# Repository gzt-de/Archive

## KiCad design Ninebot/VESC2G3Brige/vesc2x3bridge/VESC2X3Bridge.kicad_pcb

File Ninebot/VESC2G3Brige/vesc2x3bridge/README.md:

# VESC2X3Bridge

This repository provides the PCB files for the VESC2X3Bridge board. It allows an almost plug-and-play installation, with minimal configuration required on both the VESC and Bridge sides.

Community Telegram channel [Ninebot Bridges](https://t.me/NinebotBridges)

[Demo Video with my Firmware](https://youtu.be/Sf85hNRvy-E)

Also check out this repository which is used to drive the lights on your X3 Series Scooter [LightBoard](https://gitea.overkill.cc/morss12/LightBoard.git)

# Features & Abilities

A simple overview of everything the VESC2G3Bridge can do.

## What Is It?

The VESC2X3Bridge is a project I started at the end of 2025. It aims to integrate the X3 Scooter Series from Ninebot into the world of VESC, an open-source project by Benjamin Vedder.
The VESC2G3Bridge is a small computer that sits between your scooter's motor controller (VESC) and its dashboard (G3). Without it, the dashboard and the motor controller don't understand each other — the bridge acts like a translator so they can work together.

## What It Does

### Shows Your Speed
The device reads how fast the motor is spinning and works out your actual riding speed. It then sends that number to the dashboard so you can see it while you ride.

### Shows Battery Level
It checks how much battery you have left and tells the dashboard, so you always know when to charge.

### Controls the Lights
- Turns on the **rear light** just like the stock X3 Series.
- Flashes the **left and right indicators** (turn signals) when you signal a turn.
- Supports **horn** activation from the dashboard button (GT3).

### Switches Ride Profiles
The scooter can have different power modes (WALK,ECO,NORMAL,SPORT). The bridge listens to the dashboard buttons and tells the VESC which mode to switch to. You can also set it to block the switching of modes when the battery is low, bypassing the dashboards auto apply of a slow profile.

### Controls the Throttle and Brake
By running a small script on the VESC, the VESC can directly read the inputs from the dashboard, giving the VESC full control over how you accelerate and slow down.

### Updates Itself Over Wi-Fi
The device creates its own Wi-Fi network and you can upload new firmware right from your phone or computer's web browser.

### Has a Built-In Settings Page
Connect to its Wi-Fi and open a web page to change settings. [Config page](https://192.168.5.1/)

### Works With Different Battery Systems
Some scooter battery packs have their own battery management board (BMS). The bridge can read battery info from:
- The VESC itself
- The Ninebot Original BMS
- A JBD (Xiaoxiang) BMS

### Supports Two Board Versions
There are two hardware versions of the board (V1.0 and V2.1+). You pick which one you have in the settings page and the device automatically uses the right pins.

### Tracks Multiple Motor Controllers
If your scooter has more than one VESC (e.g. dual motors), the bridge reads speed data from all of them and averages the values together for a smooth, accurate speed reading.

## Quick Summary Table

| Feature | What it means |
|---|---|
| X3 Series Support | Supports G3, ZT3 and GT3* |
| Speed display | Shows km/h on the dashboard |
| Battery display | Shows battery % on the dashboard |
| Turn signals | Flashes left/right lights |
| Rear light | Controls the back light |
| Horn | Support for the GT3 horn |
| Ride profiles | Switches power modes from the dashboard |
| Low battery lock | Blocks the dashboard profile application when the battery is low |
| Throttle & brake | VESC reads the throttle and brake directly from the Dashboard |
| Wi-Fi OTA updates | Update firmware from a browser |
| Web config page | Change settings from a browser |
| Multiple BMS support | Works with VESC, Ninebot, or JBD battery boards |
| Two board versions | Supports V1.0 and V2.1+ hardware |
| Multi-VESC support | Handles more than one motor controller |

*This device was originally developed for the G3
---

## How to create a PCB from the files

1. Clone this repository and open it with KiCad.  
2. Use the **"Fabrication Outputs"** option to generate the required files for your PCB manufacturer.

3. Upload the files to a PCB manufacturer (for example, JLCPCB) and choose a 2-layer PCB board.  
4. Once you receive your PCB, development can begin. :)

## Firmware flashing

1. The board uses an **ESP32-S3-WROOM-1** chip, which has exposed USB D+, D-, and GND pins on the PCB.  
2. Use these pins to connect a USB cable to your computer and flash your firmware.

## Flashing Service

We offer a PCB flashing service for those who prefer a ready-to-use board:  

- **Cost:** Listed on our [shop page](https://scooter-labs.com/shop)  
- **Includes:** Lifetime free firmware updates  
- **How it works:** Simply order the service, and we will program your PCB with the latest firmware and ship it to you ready to use.  

This service is optional — you can still build and flash the PCB yourself if you prefer.

---

# License
This PCB design is released under the [CC BY-NC-SA 4.0 License](https://creativecommons.org/licenses/by-nc-sa/4.0/).

## What you can do
- Share and adapt this design for personal or hobby purposes
- Give credit to the original author (Finn Tews)

## What you cannot do
- Use this design for commercial purposes
- Remove or obscure attribution
- Re-license derivatives under more restrictive terms

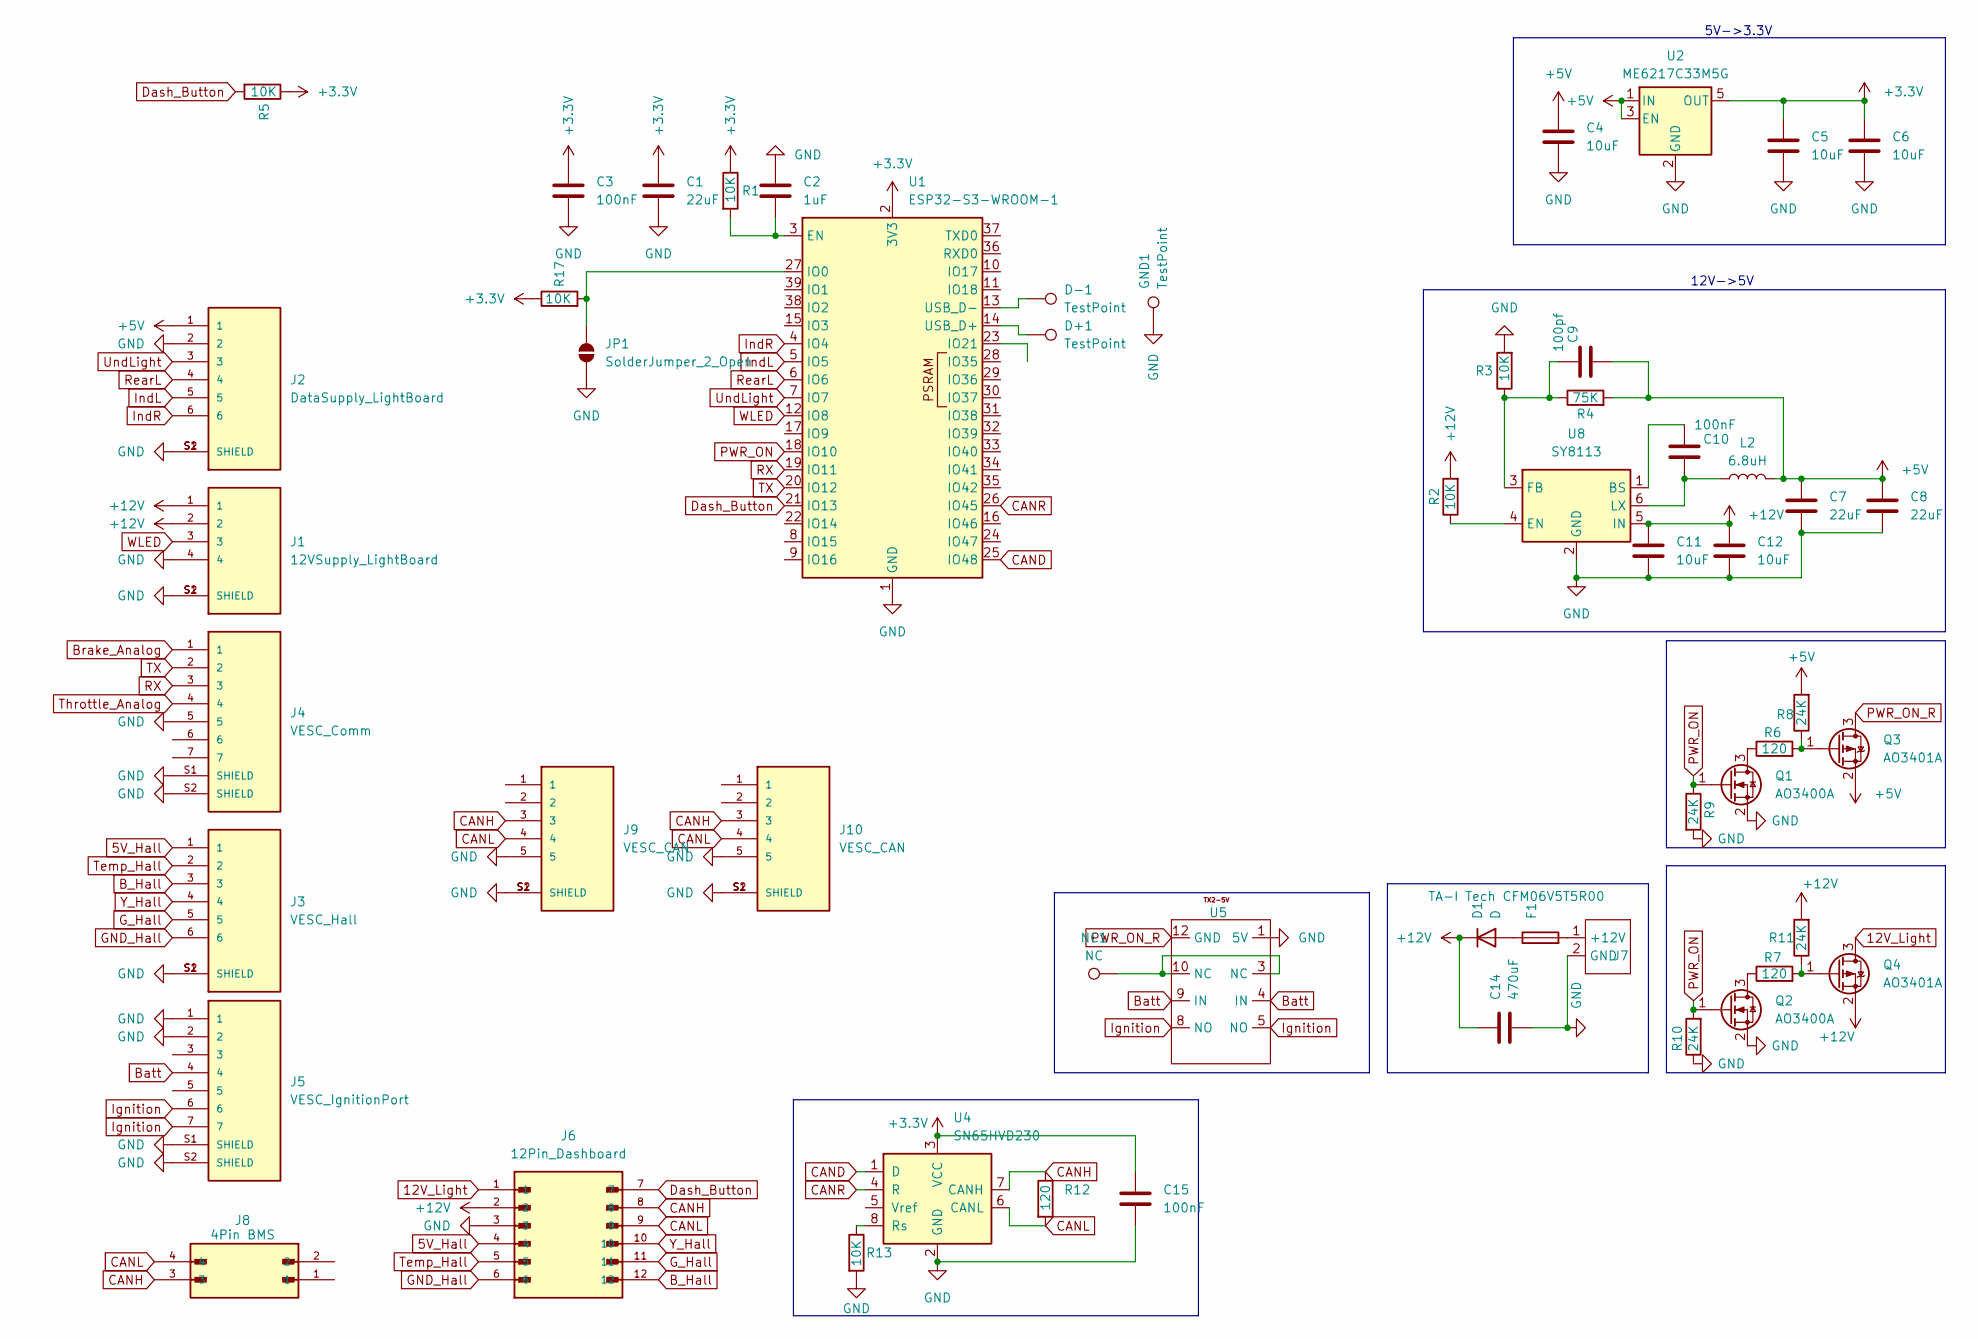
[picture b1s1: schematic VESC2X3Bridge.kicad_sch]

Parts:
C1: 22uF; C_0603_1608Metric; LCSC C86295
C2: 1uF; C_0603_1608Metric; LCSC C95843
C3, C10: 100nF; C_0603_1608Metric; LCSC C66501
C4, C5, C6: 10uF; C_0603_1608Metric; LCSC C19702
C7, C8: 22uF; C_0805_2012Metric; LCSC C29277
C9: 100pf; C_0603_1608Metric; LCSC C14858
C11, C12: 10uF; C_0805_2012Metric; LCSC C15850
C14: 470uF; CP_Radial_D8.0mm_P3.50mm; LCSC C2831775
C15: 100nF; C_0603_1608Metric_Pad1.08x0.95mm_HandSolder; LCSC C66501
D1: D; ST_D_SMC; LCSC C72264
D+1: TestPoint; TestPoint_Pad_D1.0mm
D-1: TestPoint; TestPoint_Pad_D1.0mm
F1: TA-I Tech CFM06V5T5R00; Fuse_0603_1608Metric; LCSC C911441
GND1: TestPoint; TestPoint_Pad_D1.0mm
J1: 12VSupply_LightBoard; JST_BM04B-GHS-TBT_LF__SN__N_; PARTREV N/A
J2: DataSupply_LightBoard; JST_BM06B-GHS-TBT_LF__SN__N_; PARTREV N/A; LCSC C189892
J3: VESC_Hall; JST_BM06B-GHS-TBT_LF__SN__N_; PARTREV N/A
J4: VESC_Comm; JST_BM07B-GHS-TBT_LF__SN__N_; PARTREV N/A; LCSC C378970
J5: VESC_IgnitionPort; JST_BM07B-GHS-TBT_LF__SN__N_; PARTREV N/A; LCSC C378970
J6: 12Pin_Dashboard; MOLEX_39288120; PARTREV M4; LCSC C240830
J7: WJ500V-5.08-4P; LCSC C8465
J8: 4Pin BMS; MOLEX_39281043; PARTREV M4; LCSC C240829
J9, J10: VESC_CAN; JST_BM05B-GHS-TBT_LF__SN__N_; PARTREV N/A; LCSC C189892
JP1: SolderJumper_2_Open; SolderJumper-2_P1.3mm_Open_RoundedPad1.0x1.5mm
L2: 6.8uH; SLO0530H6R8MTT; LCSC C325965
NC1: NC; TestPoint_Pad_D1.0mm
Q1, Q2: AO3400A; SOT-23; LCSC C20917
Q3, Q4: AO3401A; SOT-23; LCSC C15127
R1, R2, R3, R5, R17: 10K; R_0603_1608Metric; LCSC C98220
R4: 75K; R_0603_1608Metric; LCSC C23242
R6, R7: 120; R_0603_1608Metric; LCSC C22787
R8, R9, R10, R11: 24K; R_0603_1608Metric; LCSC C2930081
R12: 120; R_0603_1608Metric_Pad0.98x0.95mm_HandSolder; LCSC C22787
R13: 10K; R_0603_1608Metric_Pad0.98x0.95mm_HandSolder; LCSC C98220
U1: ESP32-S3-WROOM-1; LCSC C2913204
U2: ME6217C33M5G; SOT-23-5; LCSC C427602
U4: SN65HVD230; SOIC-8_3.9x4.9mm_P1.27mm; LCSC C1543812
U5: TX2-5V; LCSC C192257
U8: SY8113; SOT-23-6; LCSC C479075

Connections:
5V_Hall: J3.1, J6.4
12V_Light: J6.1, Q4.3 (D)
+3.3V: C1.1, C3.1, C5.1, C6.1, C15.1, R1.1, R5.1, R17.1, U1.2 (3V3), U2.5 (OUT), U4.3 (VCC)
+5V: C4.1, C7.1, C8.1, C9.2, J2.1, L2.2, Q3.2 (S), R4.2, R8.2, U2.1 (IN), U2.3 (EN)
+12V: C11.1, C12.1, C14.1, D1.1 (K), J1.1, J1.2, J6.2, Q4.2 (S), R2.2, R11.2, U8.5 (IN)
B_Hall: J3.3, J6.12
Batt: J5.4, U5.4 (IN), U5.9 (IN)
Brake_Analog: J4.1
CAND: U1.25 (IO48), U4.1 (D)
CANH: J6.8, J8.3, J9.3, J10.3, R12.1, U4.7 (CANH)
CANL: J6.9, J8.4, J9.4, J10.4, R12.2, U4.6 (CANL)
CANR: U1.26 (IO45), U4.4 (R)
Dash_Button: J6.7, R5.2, U1.21 (IO13)
GND: C1.2, C2.1, C3.2, C4.2, C5.2, C6.2, C7.2, C8.2, C11.2, C12.2, C14.2, C15.2, GND1.1, J1.4, J1.S1 (SHIELD), J1.S2 (SHIELD), J2.2, J2.S1 (SHIELD), J2.S2 (SHIELD), J3.S1 (SHIELD), J3.S2 (SHIELD), J4.5, J4.S1 (SHIELD), J4.S2 (SHIELD), J5.1, J5.2, J5.S1 (SHIELD), J5.S2 (SHIELD), J6.3, J7.2 (GND), J9.5, J9.S1 (SHIELD), J9.S2 (SHIELD), J10.5, J10.S1 (SHIELD), J10.S2 (SHIELD), JP1.1 (A), Q1.2 (S), Q2.2 (S), R3.2, R9.2, R10.1, R13.2, U1.1 (GND), U1.40 (GND), U1.41 (GND), U2.2 (GND), U4.2 (GND), U5.1 (5V), U8.2 (GND)
GND_Hall: J3.6, J6.6
G_Hall: J3.5, J6.11
Ignition: J5.6, J5.7, U5.5 (NO), U5.8 (NO)
IndL: J2.5, U1.5 (IO5)
IndR: J2.6, U1.4 (IO4)
unnamed: D1.2 (A), F1.1
unnamed: F1.2, J7.1 (+12V)
unnamed: JP1.2 (B), R17.2, U1.27 (IO0)
unnamed: NC1.1, U5.3 (NC), U5.10 (NC)
unnamed: Q1.3 (D), R6.1
unnamed: Q2.3 (D), R7.1
unnamed: Q3.1 (G), R6.2, R8.1
unnamed: Q4.1 (G), R7.2, R11.1
unnamed: C2.2, R1.2, U1.3 (EN)
unnamed: D+1.1, U1.14 (USB_D+)
unnamed: D-1.1, U1.13 (USB_D-)
unnamed: R13.1, U4.8 (Rs)
unnamed: C10.1, U8.1 (BS)
unnamed: R2.1, U8.4 (EN)
unnamed: C9.1, R3.1, R4.1, U8.3 (FB)
unnamed: C10.2, L2.1, U8.6 (LX)
PWR_ON: Q1.1 (G), Q2.1 (G), R9.1, R10.2, U1.18 (IO10)
PWR_ON_R: Q3.3 (D), U5.12 (GND)
RX: J4.3, U1.19 (IO11)
RearL: J2.4, U1.6 (IO6)
TX: J4.2, U1.20 (IO12)
Temp_Hall: J3.2, J6.5
Throttle_Analog: J4.4
UndLight: J2.3, U1.7 (IO7)
WLED: J1.3, U1.12 (IO8)
Y_Hall: J3.4, J6.10

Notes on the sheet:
12V->5V
5V->3.3V

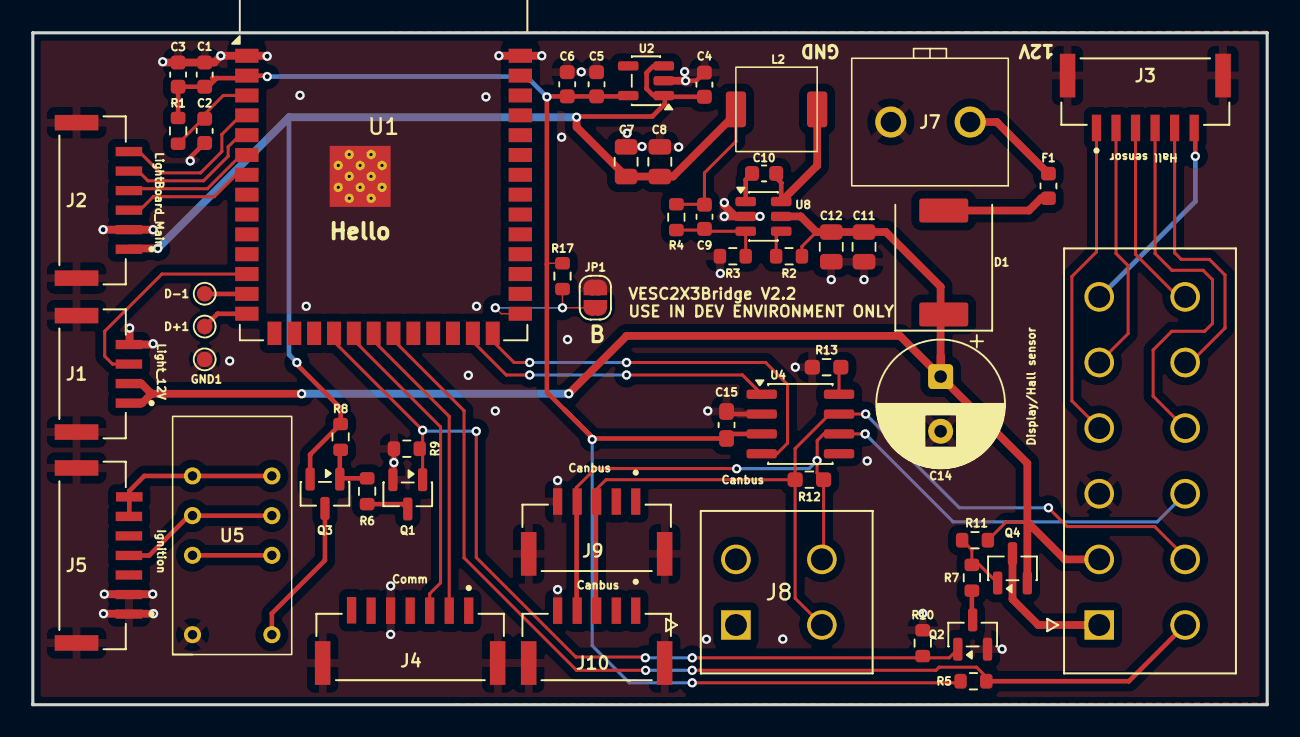
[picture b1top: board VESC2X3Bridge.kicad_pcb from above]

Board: 2 copper layers, 79.0 x 43.0 mm, 54 parts (0 on the bottom side), 43 nets.

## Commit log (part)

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2026-03-23 Moved my 2 repos to one
2026-03-23 github.com/MacintoshKeyboardHacking/segMod
2026-03-31 Read my added Information!
    supposedly same as ghost firmware except is for g3 and zt3 but with the "Panic-Button" (i lookt at it quick at it, its not for the g3)
    ! idk if it works or not !
    message from i got with it:
    🚀 SEGWAY TUNING GUIDE
    Modelle: ZT3 • G3 • GT3 • F3
    👉 Folge allen Schritten sorgfältig!
2026-04-03 Rename Info.readme to Info.md
2026-04-03 Rename Info.md to README.md
2026-04-16 backup if i need it, Fw is encrypted.
2026-04-16 NGFW
    Backup
2026-04-26 Archived.
2026-04-28 Delete VESC2X3Bridge_V2.0.6.bin
    idk
